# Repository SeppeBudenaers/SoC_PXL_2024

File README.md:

## Ultra sound sensor

### [Block design](VHDL/HC_SR04.pdf)

### [Code](VHDL/HC_SR04/vitis/Ultrasoon/src)

### [Video](https://www.youtube.com/shorts/eBlgeqNFo5I) 

## Motor + Speed sensor (WIP)
### [Block design](VHDL/MotorControl.pdf)

### [Code](VHDL/MotorControl/vitis/car_test/src)

### [Video](https://www.youtube.com/watch?v=OONQ17heeKY)

## MPU
### [Block design](VHDL/IMU.pdf)

### [Code](VHDL/IMU/vitis/IMU_TEST/src)

### [Video](https://www.youtube.com/watch?v=I253TAm4El0) 

## FULL ROOMBA

### [Block design](VHDL/MotorControl.pdf)

### [Code](VHDL/MotorControl/vitis/Roomba/src)

### Video (WIP)

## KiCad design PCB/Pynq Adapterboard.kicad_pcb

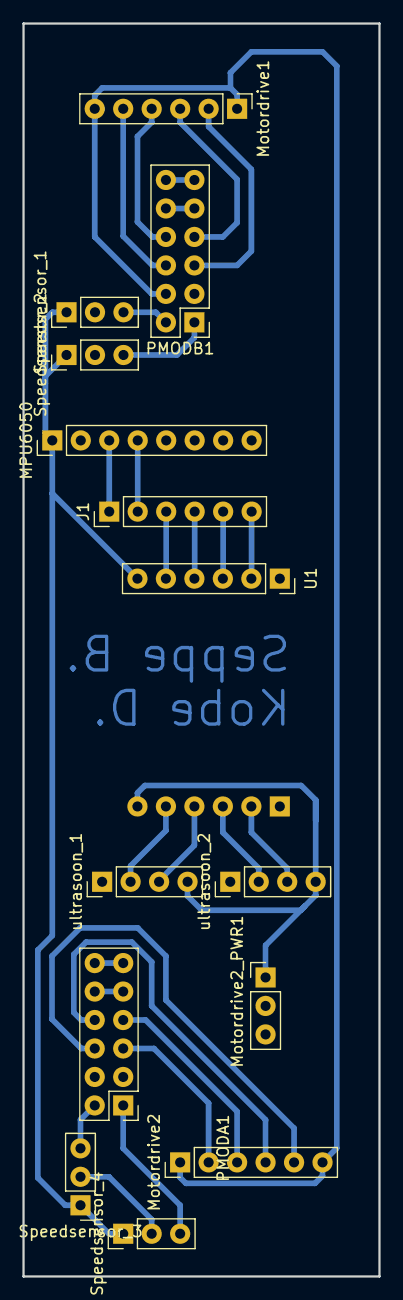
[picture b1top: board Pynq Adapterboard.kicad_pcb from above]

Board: 2 copper layers, 31.7 x 111.8 mm, 14 parts (0 on the bottom side), 26 nets.

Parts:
J1: Conn_01x06_Pin; PinHeader_1x06_P2.54mm_Vertical
MPU6050: Conn_01x08_Pin; PinHeader_1x08_P2.54mm_Vertical
Motordrive1, Motordrive2: Conn_01x06_Pin; PinHeader_1x06_P2.54mm_Vertical
Motordrive2_PWR1: Conn_01x03_Pin; PinHeader_1x03_P2.54mm_Vertical
PMODA1: Conn_02x06_Top_Bottom; PinHeader_2x06_CORRECTED
PMODB1: Conn_02x06_Top_Bottom; PinHeader_2x06_CORRECTED
Speedsensor_1, Speedsensor_2, Speedsensor_3, Speedsensor_4: Conn_01x03_Pin; PinHeader_1x03_P2.54mm_Vertical
U1: KY-051
ultrasoon_1, ultrasoon_2: Conn_01x04_Pin; PinHeader_1x04_P2.54mm_Vertical

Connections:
+3.3V: MPU6050.1, PMODA1.6, PMODA1.12, PMODB1.6, PMODB1.12, Speedsensor_1.1, Speedsensor_2.1, Speedsensor_3.1, Speedsensor_4.1, U1.VCCa
+5V: Motordrive2_PWR1.1, U1.VCCb, ultrasoon_1.4, ultrasoon_2.4
ECHO_0_3.3V: J1.3, U1.A1
ECHO_0_5V: U1.B1, ultrasoon_1.2
ECHO_1_3.3V: J1.5, U1.A3
ECHO_1_5V: U1.B3, ultrasoon_2.2
GND: MPU6050.2, Motordrive2_PWR1.2, PMODA1.5, PMODA1.11, PMODB1.5, PMODB1.11, Speedsensor_1.2, Speedsensor_2.2, Speedsensor_3.2, Speedsensor_4.2, ultrasoon_1.1, ultrasoon_2.1
Motor_Backward_3: Motordrive2.5, PMODA1.9
Motor_Backwards_1: Motordrive1.5, PMODB1.9
Motor_Backwards_2: Motordrive1.2, PMODB1.3
Motor_Backwards_4: Motordrive2.2, PMODA1.3
Motor_Enable_1: Motordrive1.1, Motordrive1.6, Motordrive2.1, Motordrive2.6, PMODB1.8
Motor_Forward_1: Motordrive1.4, PMODB1.10
Motor_Forward_3: Motordrive2.4, PMODA1.10
Motor_Forward_4: Motordrive2.3, PMODA1.4
Motor_Forwards_2: Motordrive1.3, PMODB1.4
SCL: J1.1, MPU6050.3
SDA: J1.2, MPU6050.4
Speed_1: PMODB1.7, Speedsensor_1.3
Speed_2: PMODB1.1, Speedsensor_2.3
Speed_3: PMODA1.7, Speedsensor_3.3
Speed_4: PMODA1.1, Speedsensor_4.3
TRIGGER_0_3.3V: J1.4, U1.A2
TRIGGER_0_5V: U1.B2, ultrasoon_1.3
TRIGGER_1_3.3V: J1.6, U1.A4
TRIGGER_1_5V: U1.B4, ultrasoon_2.3

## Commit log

2024-02-23 added dice and sevensegment
2024-02-23 neopixel
2024-02-23 Added HC_SR04
2024-02-26 Custon AXI block VHDL
2024-03-01 Made custom IP block
2024-03-15 HC_SRO4 block
2024-03-15 Ultrasoon works
2024-03-17 added Block Design HCSR04
2024-03-22 here
2024-03-22 added speedsensor ip_repo
2024-03-22 Added testproject for the speedsensor
2024-03-22 speed sensors works
    just wierd speed cm/(s/10)
2024-04-16 les big
2024-04-26 Working Four motors
2024-04-26 Generatef the final car files
2024-04-26 IMU finished
2024-04-26 Added car program in vitis
2024-04-27 HW_Debug
2024-04-27 readme
2024-05-02 hocuspocus delitus
2024-05-02 this works
2024-05-02 Added FinalCar
2024-05-02 hopefully thisworks speedsensor
2024-05-02 Rerun implementation, new xsa
2024-05-02 Motor control works
2024-05-02 IMUYT
2024-05-11 Added Roomba application
2024-05-11 added basic concept
2024-05-12 added pcb
2024-05-12 added addresstruct
2024-05-12 Added KY-051
2024-05-12 pcb needs design
2024-05-12 pcb done
2024-05-12 const gives error
2024-05-13 some files cobe deleted
2024-05-13 Motorstruct is kind of not the greatest idea :100:
2024-05-13 added sensors.h, and a basic main structure :+1:
2024-05-13 writing IO won't work
2024-05-13 it works
2024-05-14 added AVG speed
2024-05-17 imu added to adressstruct
2024-05-19 Car works except IMU Turning
2024-05-21 typo
2024-05-24 buh vitis bullshit
2024-05-24 fine tuned the drive
2024-05-27 this final
2024-05-27 final car worky
2024-06-10 RGB goes BRRRRRRRRR
2024-06-10 serial print works
2024-06-10 oops extra files
2024-06-10 oops
2024-06-11 examen
